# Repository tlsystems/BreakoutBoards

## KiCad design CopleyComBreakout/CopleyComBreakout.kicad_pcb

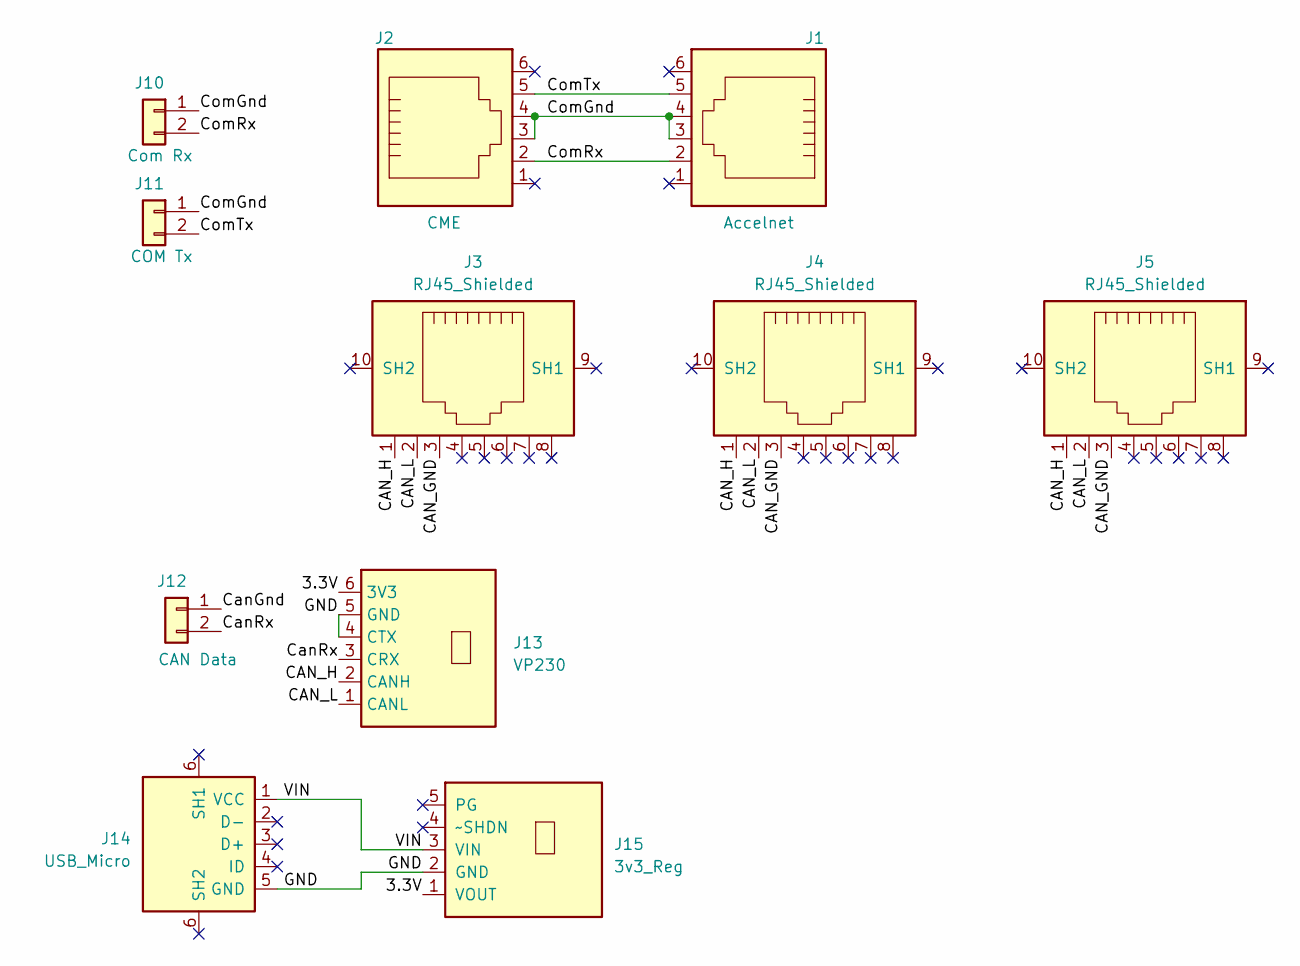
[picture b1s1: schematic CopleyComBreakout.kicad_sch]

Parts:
J1: Accelnet; RJ12, 12.2x13 mm
J2: CME; RJ12, 12.2x13 mm
J3, J4, J5: RJ45_Shielded; RJ45_Ninigi_GE
J10: Com Rx; PinHeader_1x02_P2.54mm_Vertical
J11: COM Tx; PinHeader_1x02_P2.54mm_Vertical
J12: CAN Data; PinHeader_1x02_P2.54mm_Vertical
J13: VP230; VP230 Breakout
J14: USB_Micro; USB_Micro_Breakout
J15: 3v3_Reg; Pololu Regulator

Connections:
/3.3V: J13.6 (3V3), J15.1 (VOUT)
/CAN_GND: J3.3, J4.3, J5.3
/CAN_H: J3.1, J4.1, J5.1, J13.2 (CANH)
/CAN_L: J3.2, J4.2, J5.2, J13.1 (CANL)
/CanGnd: J12.1
/CanRx: J12.2, J13.3 (CRX)
/ComGnd: J1.3, J1.4, J2.3, J2.4, J10.1, J11.1
/ComRx: J1.2, J2.2, J10.2
/ComTx: J1.5, J2.5, J11.2
/GND: J13.4 (CTX), J13.5 (GND), J14.5 (GND), J15.2 (GND)
/VIN: J14.1 (VCC), J15.3 (VIN)

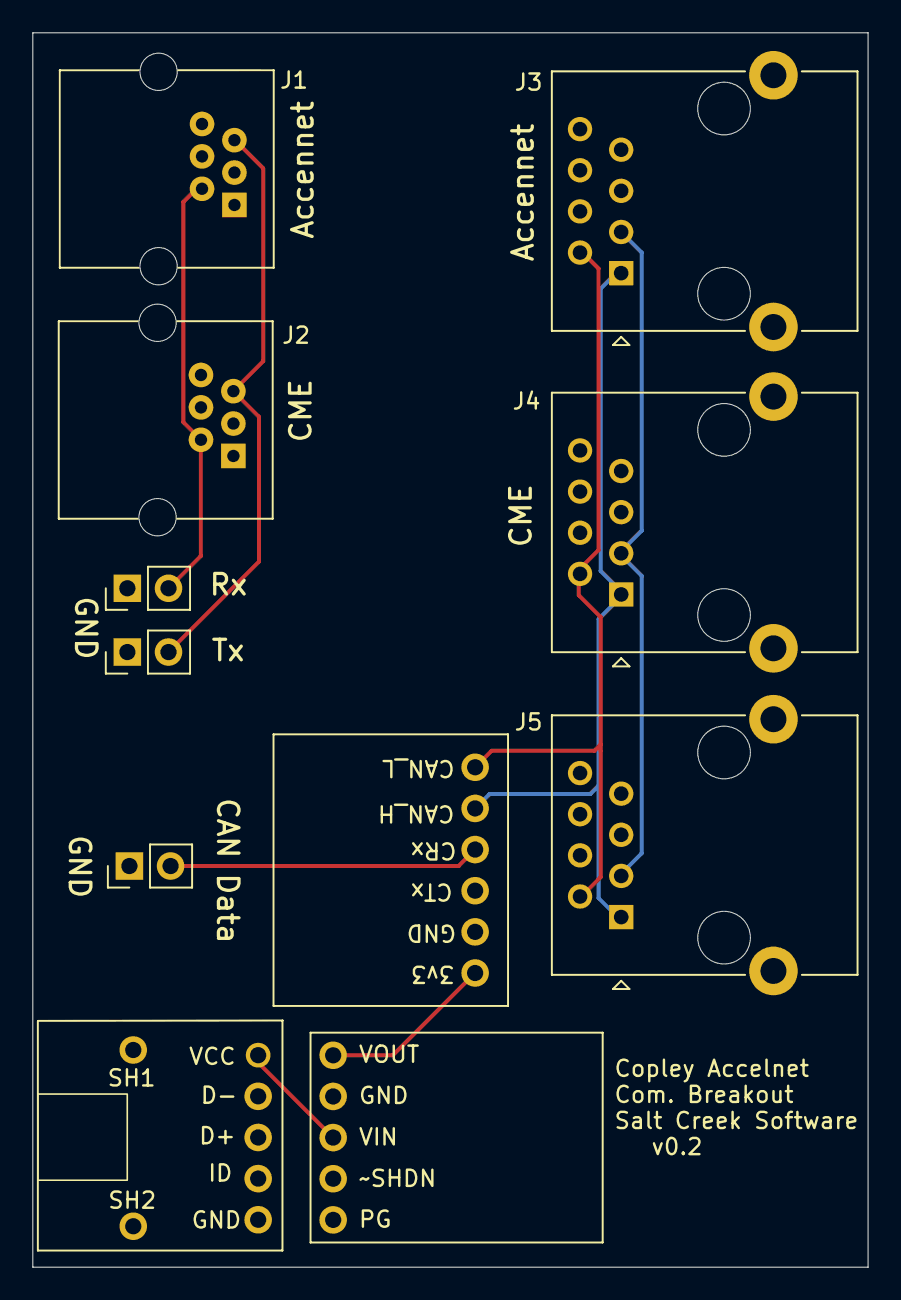
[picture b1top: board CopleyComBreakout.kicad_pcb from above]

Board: 2 copper layers, 51.6 x 76.2 mm, 11 parts (0 on the bottom side), 10 nets.

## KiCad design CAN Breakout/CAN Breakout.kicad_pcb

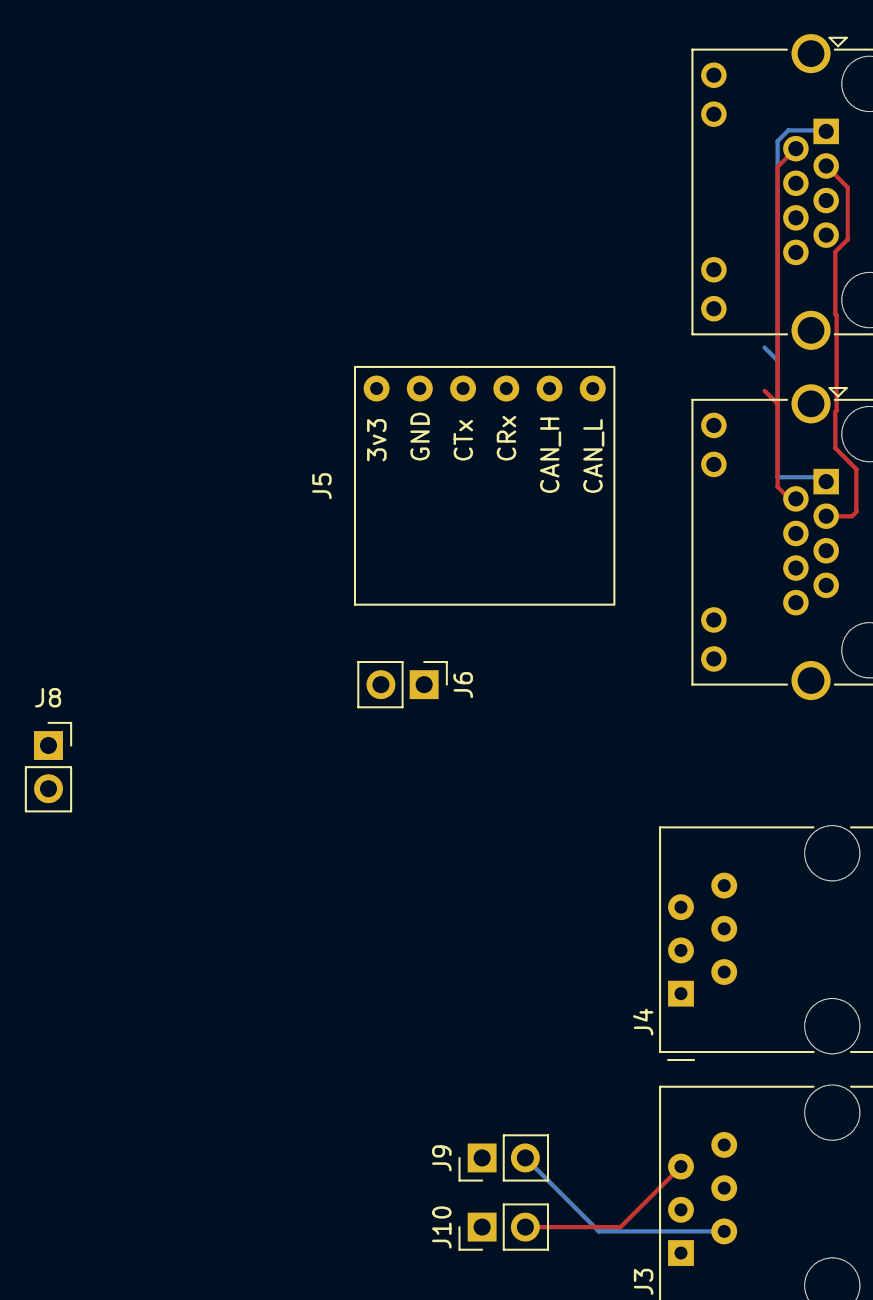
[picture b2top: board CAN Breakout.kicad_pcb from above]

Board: 2 copper layers, 9 parts (0 on the bottom side), 9 nets.

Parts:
J1, J2: RJ45; RJ45_Amphenol_RJHSE538X
J3, J4: RJ12; RJ12_Amphenol_54601
J5: VP230; VP230 Breakout
J6: CANbus Rx; PinHeader_1x02_P2.54mm_Vertical
J8: Power In; PinSocket_1x02_P2.54mm_Vertical
J9: Serial Rx; PinHeader_1x02_P2.54mm_Vertical
J10: 3; PinHeader_1x02_P2.54mm_Vertical

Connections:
CAN_Gnd: J1.3, J2.3
CAN_H: J1.1, J2.1, J5.5
CAN_L: J1.2, J2.2, J5.6
CRx: J5.4, J6.2
ComGnd: J3.3, J3.4, J4.3, J4.4, J9.1, J10.1
ComRx: J3.2, J4.2, J9.2
ComTx: J3.5, J4.5, J10.2
GND: J5.2, J6.1, J8.1
unnamed: J1.6, J2.6

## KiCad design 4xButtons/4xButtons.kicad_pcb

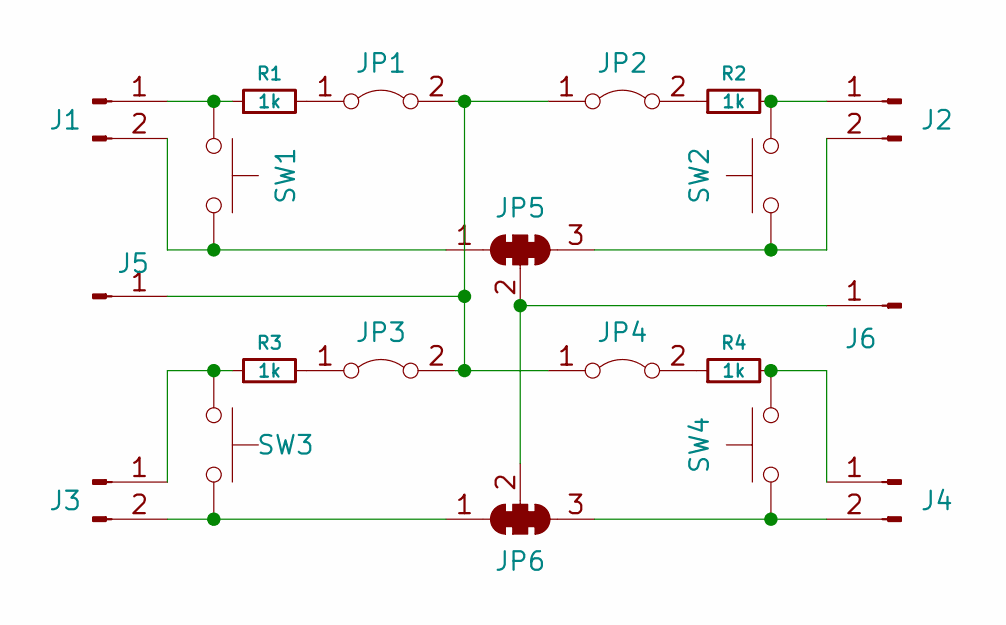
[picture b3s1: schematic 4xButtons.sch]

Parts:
J1, J2, J3, J4: Conn_01x02_Male; PinHeader_1x02_P2.54mm_Vertical
J5, J6: Conn_01x01_Male; PinHeader_1x01_P2.54mm_Vertical
JP1, JP2, JP3, JP4: Jumper_2_Bridged; SolderJumper-2_P1.3mm_Bridged_Pad1.0x1.5mm
JP5, JP6: SolderJumper_3_Bridged123; SolderJumper-3_P1.3mm_Bridged12_Pad1.0x1.5mm_NumberLabels
R1, R2, R3, R4: 1k; R_0603_1608Metric
SW1, SW2, SW3, SW4: SW_Push; SPST_PB

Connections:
unnamed: J1.1, R1.1, SW1.1
unnamed: J1.2, JP5.1 (A), SW1.2
unnamed: J2.1, R2.2, SW2.2
unnamed: J2.2, JP5.3 (B), SW2.1
unnamed: J3.1, R3.1, SW3.1
unnamed: J3.2, JP6.1 (A), SW3.2
unnamed: J4.1, R4.2, SW4.2
unnamed: J4.2, JP6.3 (B), SW4.1
unnamed: J5.1, JP1.2 (B), JP2.1 (A), JP3.2 (B), JP4.1 (A)
unnamed: J6.1, JP5.2 (C), JP6.2 (C)
unnamed: JP1.1 (A), R1.2
unnamed: JP2.2 (B), R2.1
unnamed: JP3.1 (A), R3.2
unnamed: JP4.2 (B), R4.1

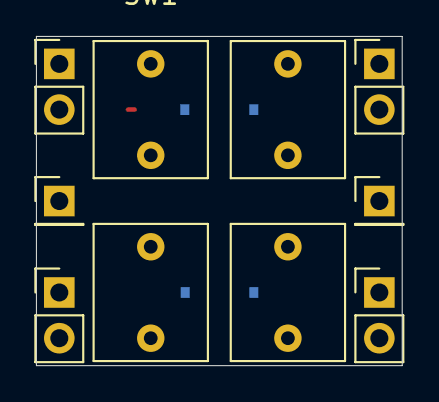
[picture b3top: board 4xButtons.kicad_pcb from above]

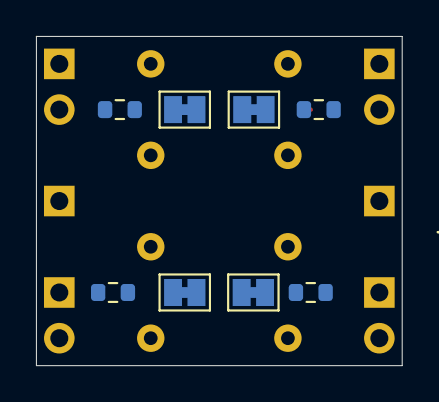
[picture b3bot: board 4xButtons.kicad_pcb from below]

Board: 2 copper layers, 20.3 x 18.3 mm, 18 parts (8 on the bottom side), 13 nets.

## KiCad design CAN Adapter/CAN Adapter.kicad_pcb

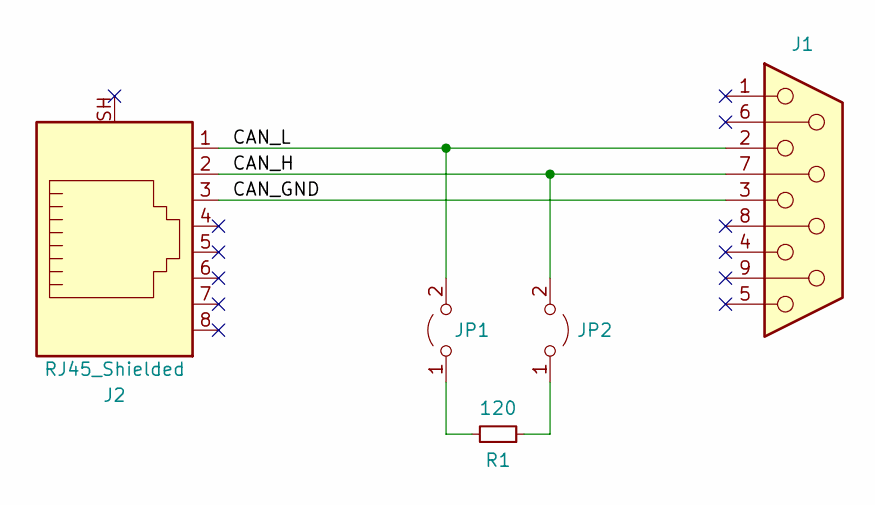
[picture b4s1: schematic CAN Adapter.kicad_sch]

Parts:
J1: DE9_Receptacle; DSUB-9_Female_EdgeMount_P2.77mm
J2: RJ45_Shielded; RJ45_Ninigi_GE
JP1, JP2: Jumper_2_Open; PinHeader_1x02_P2.54mm_Vertical
R1: 120; R_0603_1608Metric_Pad0.98x0.95mm_HandSolder

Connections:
/CAN_GND: J1.3, J2.3
/CAN_H: J1.7, J2.2, JP2.2 (B)
/CAN_L: J1.2, J2.1, JP1.2 (B)
unnamed: JP1.1 (A), R1.2
unnamed: JP2.1 (A), R1.1

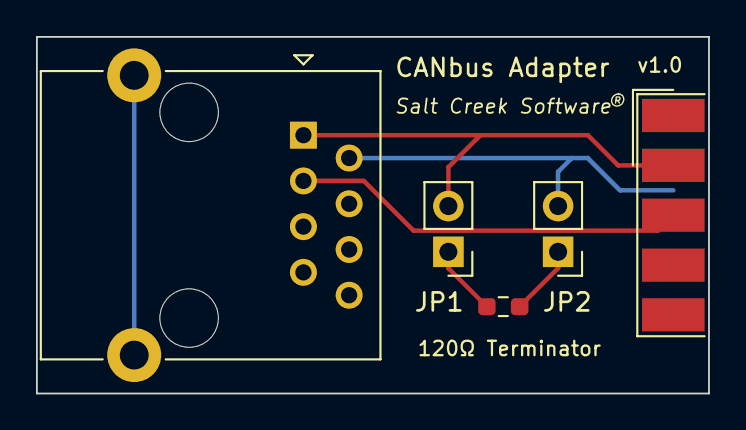
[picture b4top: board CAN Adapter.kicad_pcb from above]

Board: 2 copper layers, 37.3 x 19.8 mm, 5 parts (0 on the bottom side), 5 nets.

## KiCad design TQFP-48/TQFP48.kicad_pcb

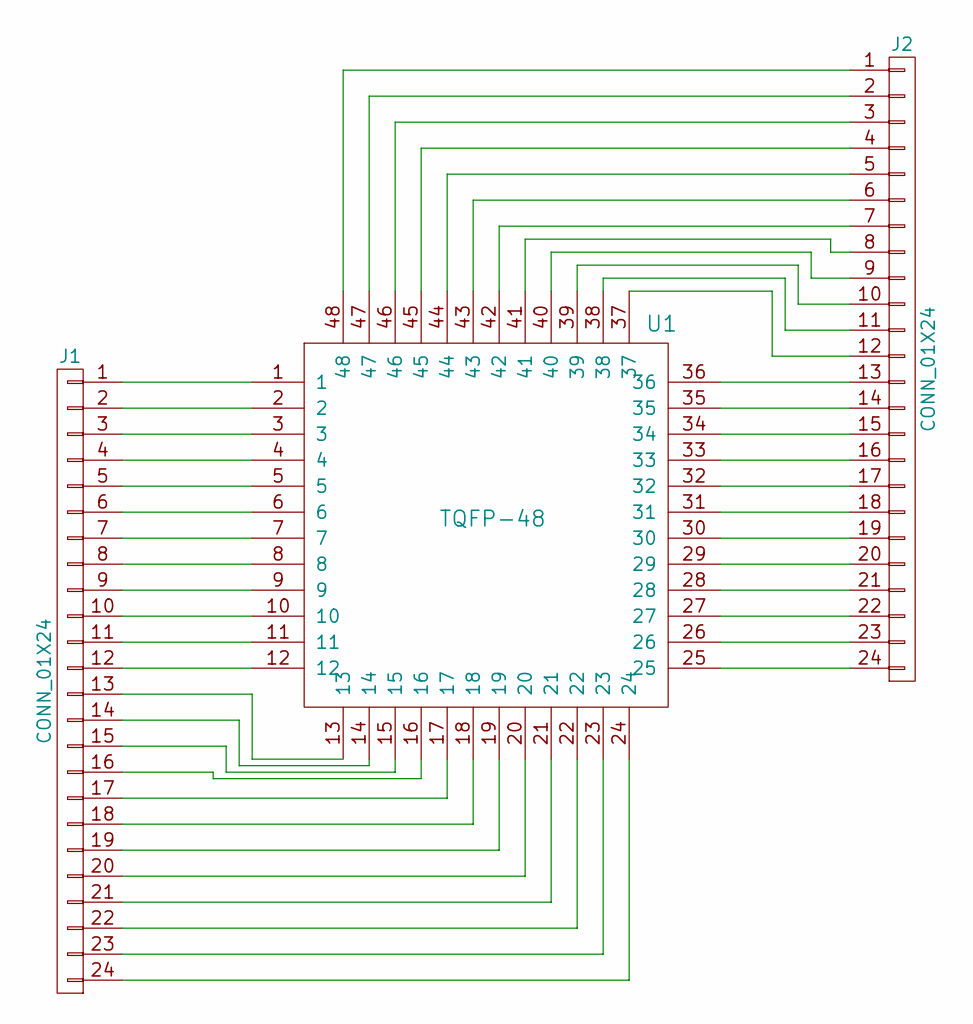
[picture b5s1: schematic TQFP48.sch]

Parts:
J1, J2: CONN_01X24; Pin_Header_Straight_1x24_Pitch2.54mm
U1: TQFP-48; TQFP-48_7x7mm_Pitch0.5mm

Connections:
unnamed: J1.1, U1.1
unnamed: J1.2, U1.2
unnamed: J1.3, U1.3
unnamed: J1.4, U1.4
unnamed: J1.5, U1.5
unnamed: J1.6, U1.6
unnamed: J1.7, U1.7
unnamed: J1.8, U1.8
unnamed: J1.9, U1.9
unnamed: J1.10, U1.10
unnamed: J1.11, U1.11
unnamed: J1.12, U1.12
unnamed: J1.13, U1.13
unnamed: J1.14, U1.14
unnamed: J1.15, U1.15
unnamed: J1.16, U1.16
unnamed: J1.17, U1.17
unnamed: J1.18, U1.18
unnamed: J1.19, U1.19
unnamed: J1.20, U1.20
unnamed: J1.21, U1.21
unnamed: J1.22, U1.22
unnamed: J1.23, U1.23
unnamed: J1.24, U1.24
unnamed: J2.1, U1.48
unnamed: J2.2, U1.47
unnamed: J2.3, U1.46
unnamed: J2.4, U1.45
unnamed: J2.5, U1.44
unnamed: J2.6, U1.43
unnamed: J2.7, U1.42
unnamed: J2.8, U1.41
unnamed: J2.9, U1.40
unnamed: J2.10, U1.39
unnamed: J2.11, U1.38
unnamed: J2.12, U1.37
unnamed: J2.13, U1.36
unnamed: J2.14, U1.35
unnamed: J2.15, U1.34
unnamed: J2.16, U1.33
unnamed: J2.17, U1.32
unnamed: J2.18, U1.31
unnamed: J2.19, U1.30
unnamed: J2.20, U1.29
unnamed: J2.21, U1.28
unnamed: J2.22, U1.27
unnamed: J2.23, U1.26
unnamed: J2.24, U1.25

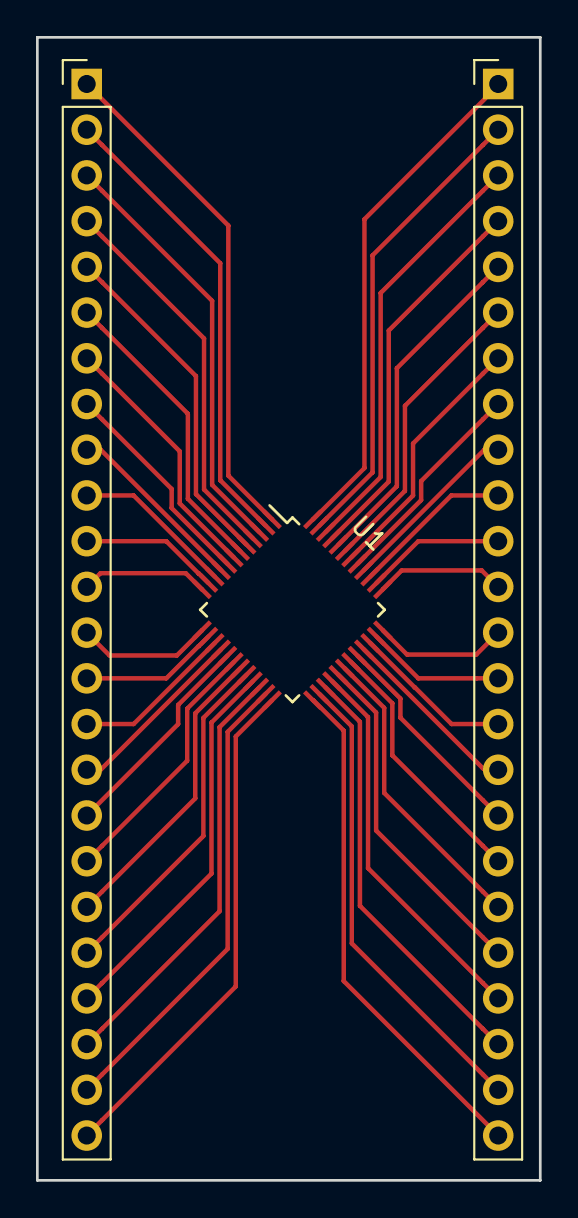
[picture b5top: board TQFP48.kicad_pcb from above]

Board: 2 copper layers, 27.9 x 63.5 mm, 3 parts (0 on the bottom side), 48 nets.

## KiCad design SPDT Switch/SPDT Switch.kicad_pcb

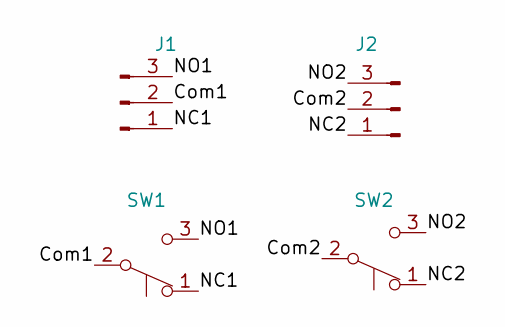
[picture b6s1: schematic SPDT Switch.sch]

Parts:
J1, J2: Conn_01x03_Male; PinHeader_1x03_P2.54mm_Vertical
SW1, SW2: SW_Push_SPDT; PinHeader_1x03_P2.54mm_Vertical

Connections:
/Com1: J1.2, SW1.2 (B)
/Com2: J2.2, SW2.2 (B)
/NC1: J1.1, SW1.1 (A)
/NC2: J2.1, SW2.1 (A)
/NO1: J1.3, SW1.3 (C)
/NO2: J2.3, SW2.3 (C)

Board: 2 copper layers, 4 parts (0 on the bottom side), 6 nets, no tracks yet.

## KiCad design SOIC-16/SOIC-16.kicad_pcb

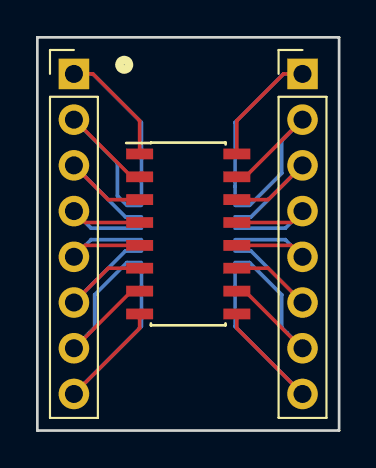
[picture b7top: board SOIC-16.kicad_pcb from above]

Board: 2 copper layers, 16.8 x 21.8 mm, 4 parts (1 on the bottom side), 15 nets.

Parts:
J1: Left; Pin_Header_Straight_1x08_Pitch2.54mm
J2: Right; Pin_Header_Straight_1x08_Pitch2.54mm
U1: SOIC; SOIC-16_3.9x9.9mm_Pitch1.27mm
U2: SSOP; SSOP-16_3.9x4.9mm_Pitch0.635mm

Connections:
/Pin1: J1.1, U1.1, U2.16
/Pin2: J1.2, U1.2, U2.15
/Pin3: J1.3, U1.3, U2.14
/Pin4: J1.4, U1.4, U2.13
/Pin5: J1.5, U1.5, U2.12
/Pin6: J1.6, U1.6, U2.11
/Pin7: J1.7, U1.7, U2.10
/Pin8: J1.8, J2.8, U1.8, U1.9, U2.8, U2.9
/Pin10: J2.7, U1.10, U2.7
/Pin11: J2.6, U1.11, U2.6
/Pin12: J2.5, U1.12, U2.5
/Pin13: J2.4, U1.13, U2.4
/Pin14: J2.3, U1.14, U2.3
/Pin15: J2.2, U1.15, U2.2
/Pin16: J2.1, U1.16, U2.1

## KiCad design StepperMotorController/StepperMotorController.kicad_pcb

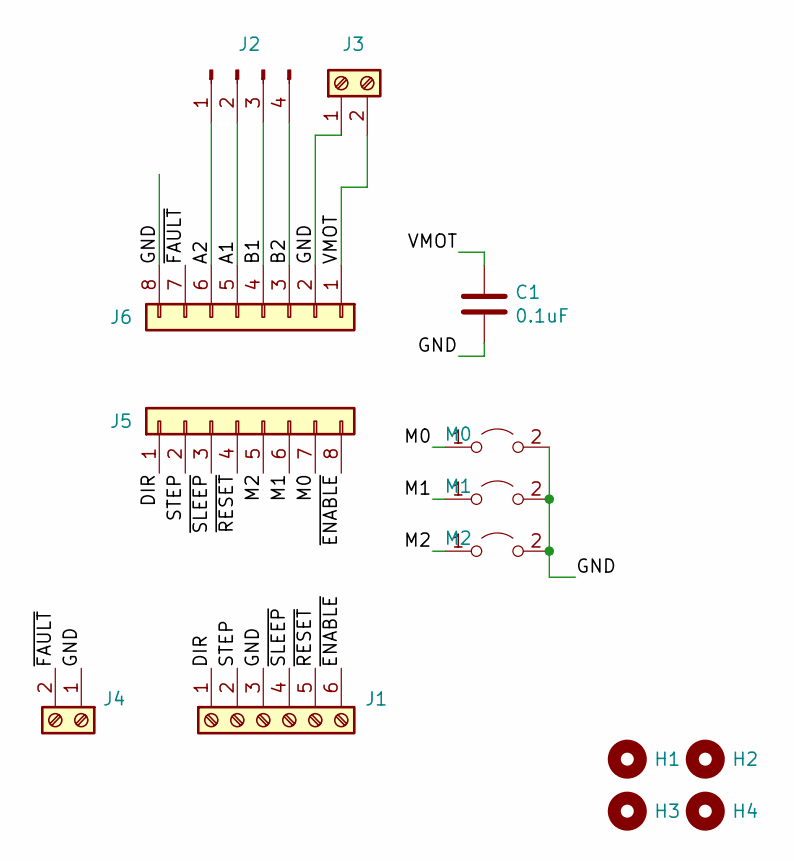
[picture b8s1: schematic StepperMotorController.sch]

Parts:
C1: 0.1uF; C_1206_3216Metric
H1, H2, H3, H4: MountingHole; MountingHole_2.7mm_M2.5
J1: Screw_Terminal_01x06; TerminalBlock_Phoenix_PT-1,5-6-3.5-H_1x06_P3.50mm_Horizontal
J2: Conn_01x04_Male; JST_XH_B4B-XH-A_1x04_P2.50mm_Vertical
J3, J4: Screw_Terminal_01x02; TerminalBlock_Phoenix_PT-1,5-2-3.5-H_1x02_P3.50mm_Horizontal
J5, J6: Conn_01x08; PinSocket_1x08_P2.54mm_Vertical
M0, M1, M2: Jumper_2_Open; SolderJumper-2_P1.3mm_Open_RoundedPad1.0x1.5mm

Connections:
/A1: J2.2, J6.5
/A2: J2.1, J6.6
/B1: J2.3, J6.4
/B2: J2.4, J6.3
/DIR: J1.1, J5.1
/GND: C1.2, J1.3, J3.1, J4.1, J6.2, J6.8, M0.2 (B), M1.2 (B), M2.2 (B)
/M0: J5.7, M0.1 (A)
/M1: J5.6, M1.1 (A)
/M2: J5.5, M2.1 (A)
/STEP: J1.2, J5.2
/VMOT: C1.1, J3.2, J6.1
/~ENABLE: J1.6, J5.8
/~FAULT: J4.2, J6.7
/~RESET: J1.5, J5.4
/~SLEEP: J1.4, J5.3

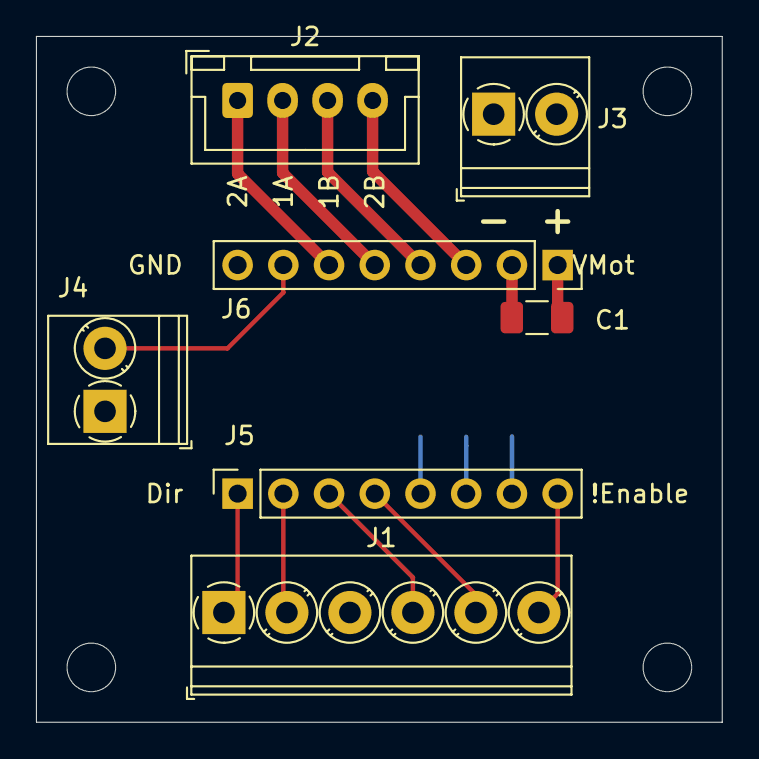
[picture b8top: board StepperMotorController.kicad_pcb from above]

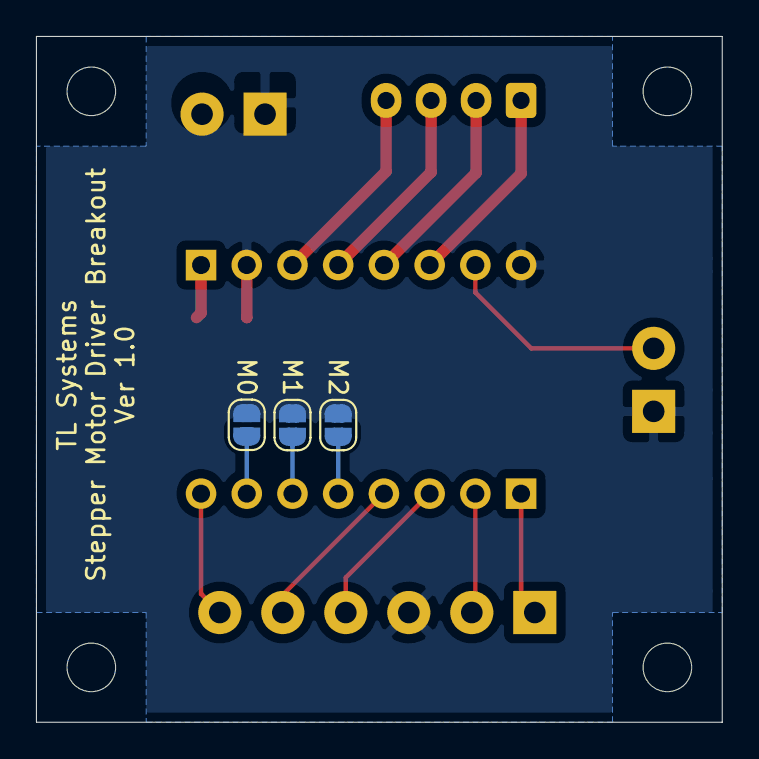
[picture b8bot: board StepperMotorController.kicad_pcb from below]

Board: 2 copper layers, 38.1 x 38.1 mm, 14 parts (3 on the bottom side), 15 nets.

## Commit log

2017-12-16 Breakout Board Footprint Library
2017-12-16 v0.2 of Dual RJ-45 Breakout Board
2017-12-16 Version 0.3 of Rotary Encoder w/debounce and LED breakout board
2017-12-16 Version 0.4 - added version and title text to back side
2017-12-16 TL Systems Breakout Board Component Library
2017-12-30 Breakout board for JST Sales mid-board Micro AB USB Connector Created to checkout newly created footprint
2017-12-30 Directory for data sheets of components used on breakout boards.
2018-01-07 Initial commit, v0.1
2018-02-22 Initial commit of TQFP-64 Breakout Board
2019-02-06 Initial commit of RJ-11 Breakout Board
2019-02-11 Rename RJ-11 for 6P6C Jack
2019-02-11 Another initial commit
2019-02-11 Initial commit V0.1
2023-10-03 CANbus DB-9 to RJ-45 adapter
2023-10-03 Change sheet size to 8.5x11
2023-12-29 Add CAN Breakout and CopleyComBreakout
